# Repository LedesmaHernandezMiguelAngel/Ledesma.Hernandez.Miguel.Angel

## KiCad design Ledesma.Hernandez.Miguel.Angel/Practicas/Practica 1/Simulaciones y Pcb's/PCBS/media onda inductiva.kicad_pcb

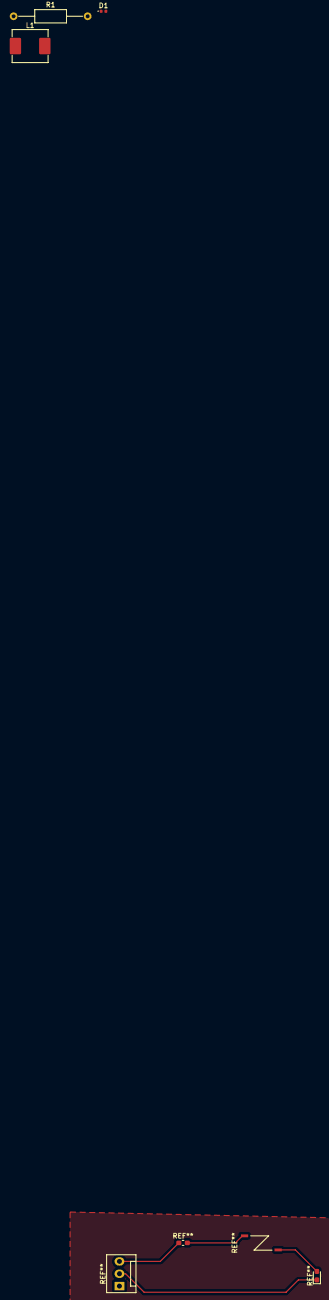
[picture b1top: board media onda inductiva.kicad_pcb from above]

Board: 2 copper layers, 3 parts (0 on the bottom side), 3 nets.

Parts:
D1: DIODE; D_0402_1005Metric
L1: 10mh; L_Abracon_ASPI-0630LR
R1: 10; R_Axial_DIN0207_L6.3mm_D2.5mm_P15.24mm_Horizontal

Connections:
AC: D1.1, R1.2
unnamed: D1.2, L1.1
unnamed: L1.2, R1.1

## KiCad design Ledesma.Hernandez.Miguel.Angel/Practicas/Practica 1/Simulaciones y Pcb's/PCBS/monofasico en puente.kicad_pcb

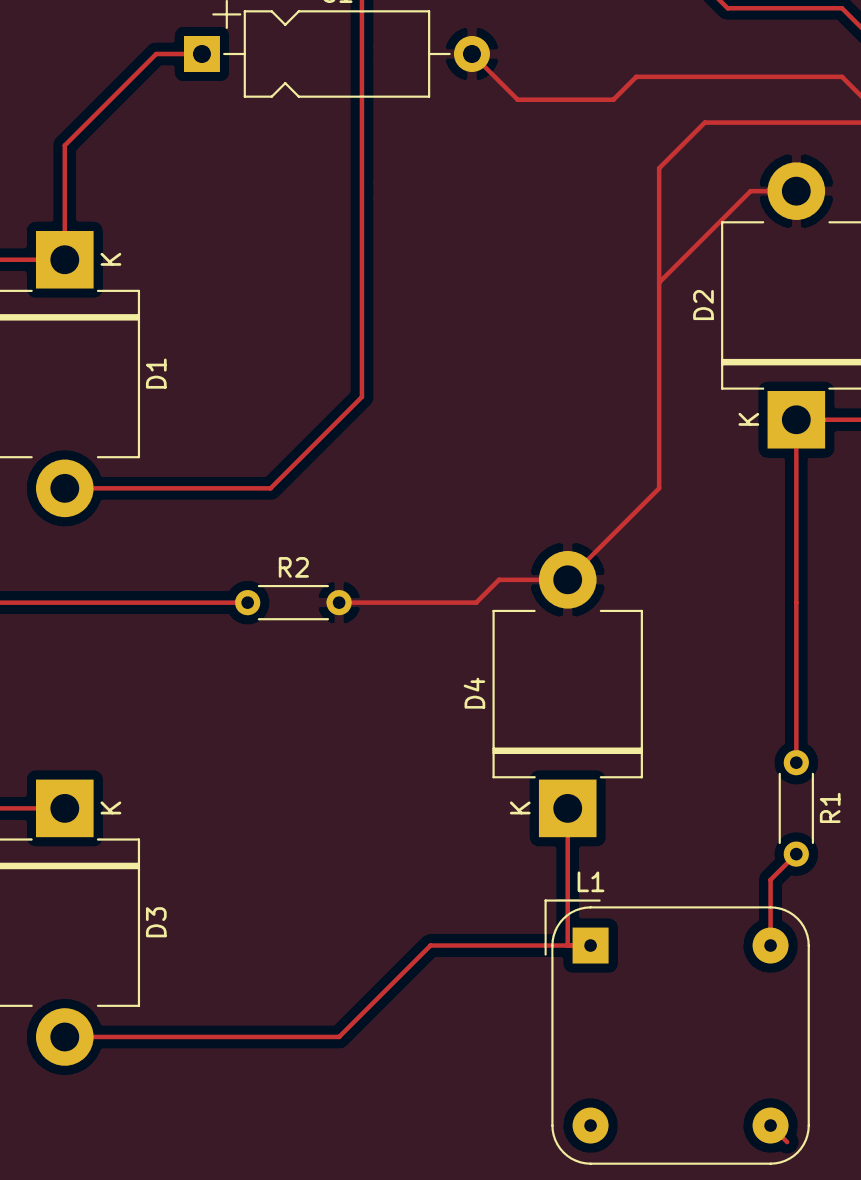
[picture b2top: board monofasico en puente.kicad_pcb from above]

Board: 2 copper layers, 8 parts (0 on the bottom side), 5 nets.

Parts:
C1: 1mf; CP_Axial_L10.0mm_D4.5mm_P15.00mm_Horizontal
D1, D2, D3, D4: D; D_5KPW_P12.70mm_Horizontal
L1: 1mh; Choke_Schaffner_RN102-04-14.0x14.0mm
R1, R2: 10; R_Axial_DIN0204_L3.6mm_D1.6mm_P5.08mm_Horizontal

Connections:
AC: D3.2, D4.1, L1.1
GNDREF: C1.2, D2.2, D4.2, R2.2
unnamed: C1.1, D1.1, D3.1, R2.1
unnamed: D1.2, D2.1, R1.1
unnamed: L1.2, R1.2

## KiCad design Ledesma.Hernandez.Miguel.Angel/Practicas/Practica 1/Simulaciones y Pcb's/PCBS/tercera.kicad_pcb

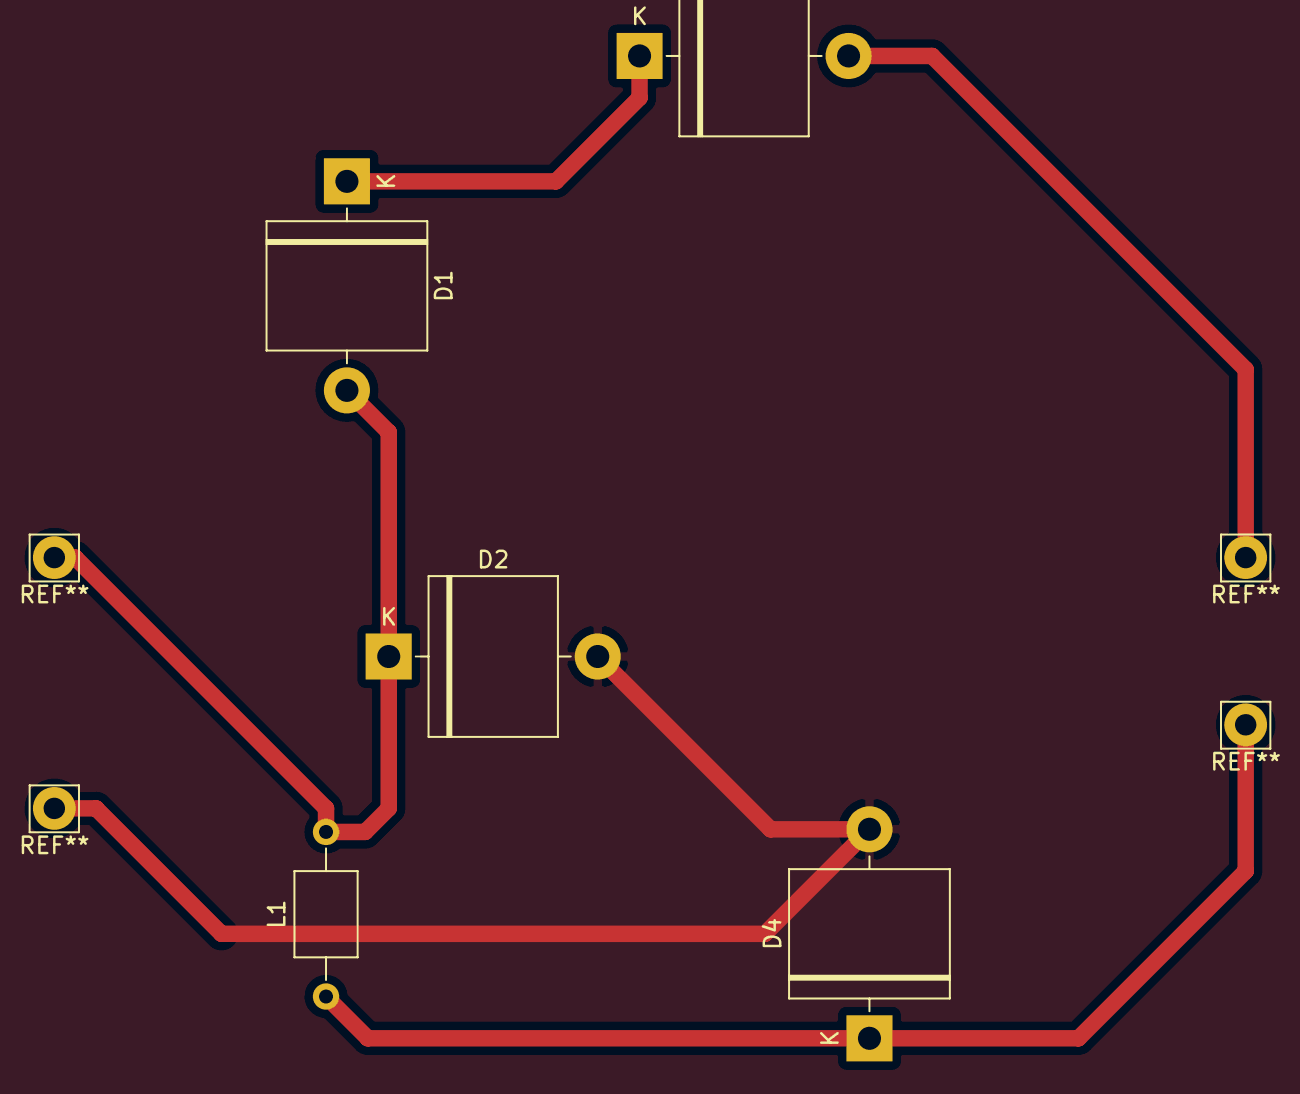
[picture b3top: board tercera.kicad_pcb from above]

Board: 2 copper layers, 5 parts (0 on the bottom side), 4 nets.

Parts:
D1, D2, D3, D4: D; D_5KP_P12.70mm_Horizontal
L1: L; L_Axial_L5.0mm_D3.6mm_P10.00mm_Horizontal_Murata_BL01RN1A2A2

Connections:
GNDREF: D2.2, D4.2
unnamed: D1.1, D3.1
unnamed: D1.2, D2.1, L1.2
VAC: D3.2, D4.1, L1.1

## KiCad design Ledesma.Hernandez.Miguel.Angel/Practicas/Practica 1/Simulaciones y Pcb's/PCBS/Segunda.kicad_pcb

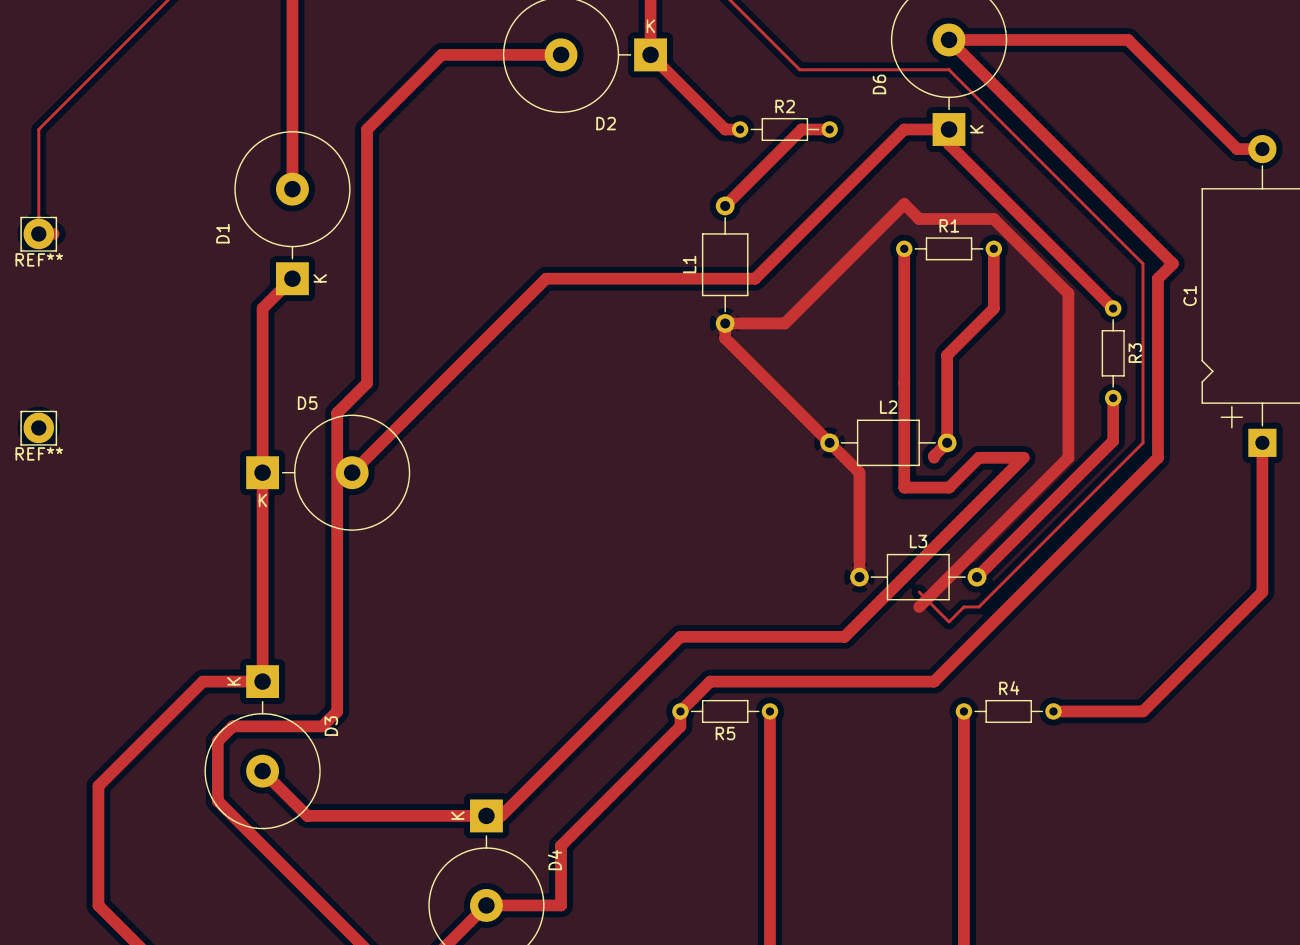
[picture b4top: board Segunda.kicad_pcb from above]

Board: 2 copper layers, 15 parts (0 on the bottom side), 10 nets.

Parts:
C1: C; CP_Axial_L18.0mm_D10.0mm_P25.00mm_Horizontal
D1, D2, D3, D4, D5, D6: D; D_5KP_P7.62mm_Vertical_KathodeUp
L1, L2, L3: L; L_Axial_L5.0mm_D3.6mm_P10.00mm_Horizontal_Murata_BL01RN1A2A2
R1, R2, R3, R4, R5: R; R_Axial_DIN0204_L3.6mm_D1.6mm_P7.62mm_Horizontal

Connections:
unnamed: C1.1, R4.2
unnamed: C1.2, D2.2, D4.2, D6.2, R5.2
unnamed: D1.1, D3.1, D5.1, R4.1, R5.1
unnamed: D1.2, D2.1, R2.1
unnamed: D3.2, D4.1, R1.1
unnamed: D5.2, D6.1, R3.1
unnamed: L1.2, R2.2
unnamed: L2.2, R1.2
unnamed: L3.2, R3.2
VAC: L1.1, L2.1, L3.1

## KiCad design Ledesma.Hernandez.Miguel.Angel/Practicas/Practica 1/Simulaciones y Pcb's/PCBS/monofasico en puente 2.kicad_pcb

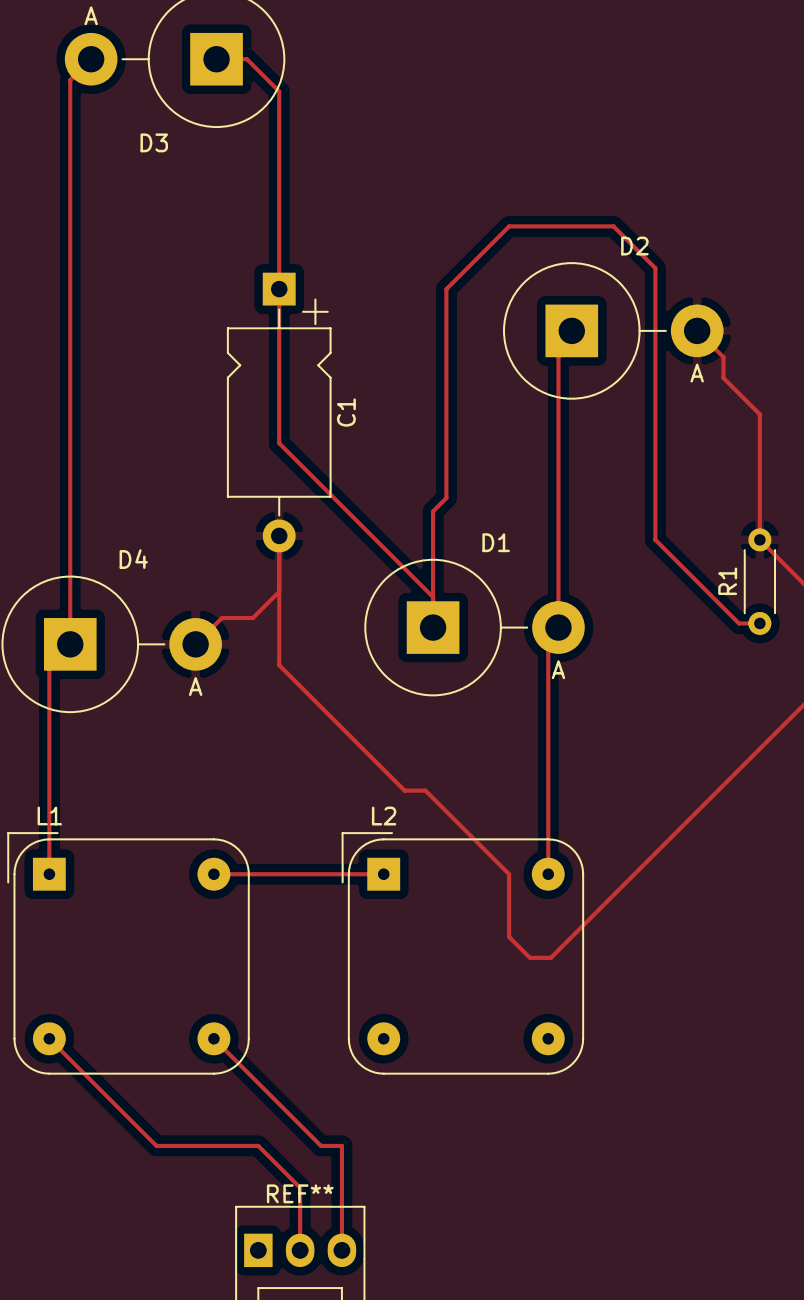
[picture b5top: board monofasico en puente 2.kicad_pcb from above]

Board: 2 copper layers, 8 parts (0 on the bottom side), 5 nets.

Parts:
C1: 1mf; CP_Axial_L10.0mm_D6.0mm_P15.00mm_Horizontal
D1, D2, D3, D4: D; D_5KPW_P7.62mm_Vertical_AnodeUp
L1: 0.5mh; Choke_Schaffner_RN102-04-14.0x14.0mm
L2: 1mh; Choke_Schaffner_RN102-04-14.0x14.0mm
R1: 10; R_Axial_DIN0204_L3.6mm_D1.6mm_P5.08mm_Horizontal

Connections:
AC: D3.2, D4.1, L1.1
GNDREF: C1.2, D2.2, D4.2, R1.2
unnamed: C1.1, D1.1, D3.1, R1.1
unnamed: D1.2, D2.1, L2.2
unnamed: L1.2, L2.1

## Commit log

2019-09-08 Matricula: 18312262
2019-09-14 caca de la vaca
2019-09-16 Matrícula : 18312262
2019-09-20 18312262
